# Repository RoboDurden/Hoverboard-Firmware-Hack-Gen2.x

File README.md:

# find your board with the 'interactive search' on the [Wiki](https://github.com/RoboDurden/Hoverboard-Firmware-Hack-Gen2.x/wiki) here :-)

# study the [Wiki](https://github.com/RoboDurden/Hoverboard-Firmware-Hack-Gen2.x/wiki) before opening a new issue !
***

### code moved to [Hoverboard-Firmware-Hack-Gen2.x-GD32](https://github.com/RoboDurden/Hoverboard-Firmware-Hack-Gen2.x-GD32) !!
### MM32 port go here [Hoverboard-Firmware-Hack-Gen2.x-MM32](https://gitlab.com/ailife8881/Hoverboard-Firmware-Hack-Gen2.x-MM32)) (FOC, speed/torque/position-control, ODrive CANSimple over UART, uartBus protocol, pinFinder over uart/browser UI)
#### MM32 EFeru FOC port go here [MM32SPIN05_Hoberboard_hack](https://github.com/trondin/MM32SPIN05_Hoberboard_hack) (no foc,but EFeru uart protocol)
both MM32 firmwares run on this $4.4 (+$5 shipping) pair of Gen2.4.2 boards: https://www.aliexpress.com/item/1005005959910034.html (tell me if you find a likewise offer that ships to Germany/EU)
***

### 2024/02/18: board numbering changed from Gen2.x to Gen2.t.v
Gen2.1.4xf = split board . target 1 . version 4 x=64kb, f=FOC capable.

The s(32kB)/x(64kB) flag and the f flag are for information only.

Targets are the Keil targets:
- 1 gd32f130 
- 2 gd/stm32f103 
- 3 gd32e230 
- 4 mm32spin0x 
- 5 lks32

## 2024/1/10 the following layouts are ready to use (99%):

- Gen2.1.1 (ex2.0)
- Gen2.1.3 (ex2.2) https://github.com/RoboDurden/Hoverboard-Firmware-Hack-Gen2.x/issues/5
- Gen2.1.4 (ex2.3) https://github.com/RoboDurden/Hoverboard-Firmware-Hack-Gen2.x/issues/20
- Gen2.1.7.1 (ex2.6.1) https://github.com/RoboDurden/Hoverboard-Firmware-Hack-Gen2.x/issues/49
- Gen2.1.8 (ex2.10) https://github.com/RoboDurden/Hoverboard-Firmware-Hack-Gen2.x/issues/25
- Gen2.1.11 (ex2.13) https://github.com/RoboDurden/Hoverboard-Firmware-Hack-Gen2.x/issues/33
- Gen2.1.16 (ex2.18) https://github.com/RoboDurden/Hoverboard-Firmware-Hack-Gen2.x/issues/40

layouts worth testing (with a 2A cc constant current power supply / dcdc-step-down converter | 1.5 42V charger):

- Gen2.1.2 (ex2.1) this repo here was a fork from a running 2.1 firmware
- Gen2.1.5 (ex2.4) https://github.com/RoboDurden/Hoverboard-Firmware-Hack-Gen2.x/issues/3
- Gen2.3.1 (ex2.7) https://github.com/RoboDurden/Hoverboard-Firmware-Hack-Gen2.x/issues/16
- Gen2.1.9 (ex2.11) https://github.com/RoboDurden/Hoverboard-Firmware-Hack-Gen2.x/issues/27
- Gen2.1.13 (ex2.15) https://github.com/RoboDurden/Hoverboard-Firmware-Hack-Gen2.x/issues/38
- Gen2.1.18 (ex2.20) https://github.com/RoboDurden/Hoverboard-Firmware-Hack-Gen2.x/issues/58
  
### Update 2.x:
- This is a fork from https://github.com/krisstakos/Hoverboard-Firmware-Hack-Gen2.1
- with different defines_2-x.h for two different board layouts :-) 
- Simply set `#define LAYOUT x` to your 2.x board in `Inc/config.h` :-))
- You can download compiled binaries [here](BinariesReadyToFlash/) (the Dummy-firmwares will ignore uart speed and will repeat speed from -300 to 300 instead)
- Binaries probably not yet working: [BinariesToTest/](BinariesToTest/)
- Make sure your board is one of the supported layouts ! **Wrong pin assignments can shortcut the battery and kill the mosfets !!**

#### Update 2.1:
- That's a fork from https://github.com/flo199213/Hoverboard-Firmware-Hack-Gen2
- Compiles with Keil version 6 :-))

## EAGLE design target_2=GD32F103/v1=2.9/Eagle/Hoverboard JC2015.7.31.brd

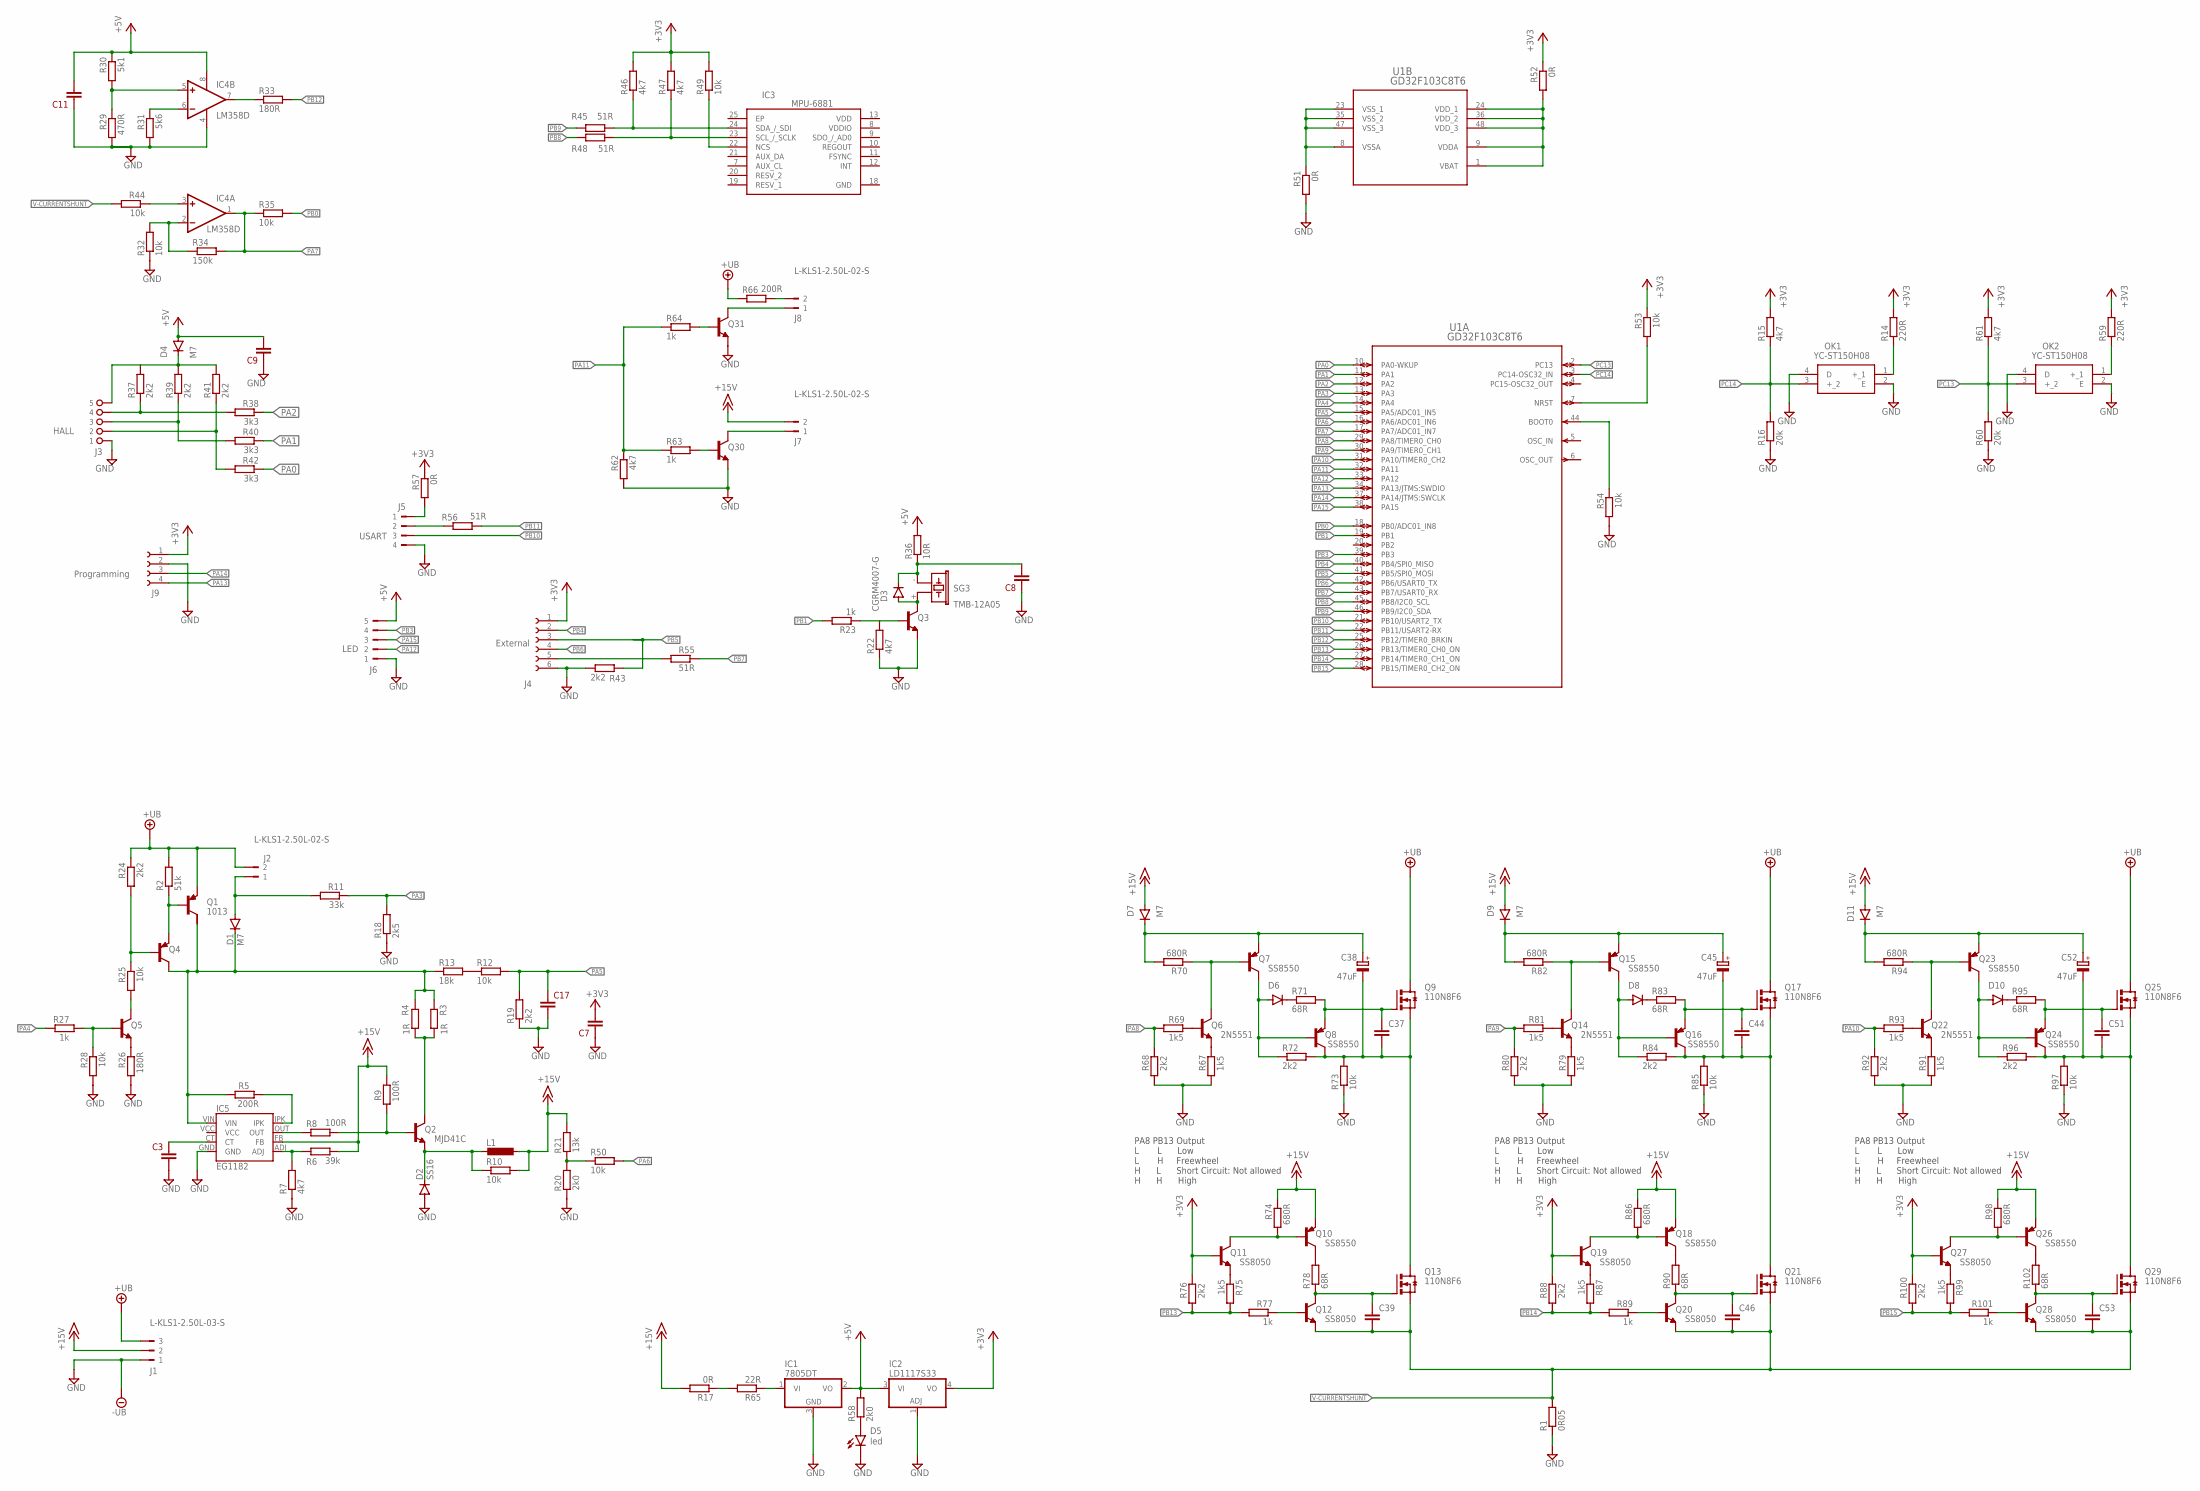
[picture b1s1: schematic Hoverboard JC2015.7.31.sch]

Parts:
C3, C7, C8, C9, C11, C17, C37, C39, C44, C46, C51, C53: C-EUC0603; C0603
C38, C45, C52: 47uF; E1,8-4
D1, D4, D7, D9, D11: M7; SOD-123_MINI-SMA
D2: SS16; DO-214AC
D3: CGRM4007-G; SOD-123_MINI-SMA
D5: led; PLCC2
D6, D8, D10: DIODE-MINIMELF; MINIMELF
IC1: 7805DT; TO252
IC2: LD1117S33; SOT223
IC3: MPU-6881; QFN40P300X300X95-25N
IC4: LM358D; SO08
IC5: EG1182
J1: L-KLS1-2.50L-03-S
J2, J7, J8: L-KLS1-2.50L-02-S
J3: HALL; ST05-1
J4: External; FE06-1
J5: USART; L-KLS1-2.50L-04-S
J6: LED; L-KLS1-2.50L-05-S
J9: Programming; FE04-1
L1: L-EU6000-XXX-RC; 6000-XXXX-RC
OK1, OK2: YC-ST150H08
Q1: 1013; SOT89
Q2: MJD41C; DPAK
Q3, Q5, Q30, Q31: MMBT5551LT1-NPN-SOT23-BEC; SOT23-BEC
Q4: MMBT540LT1-PNP-SOT23-BEC; SOT23-BEC
Q6, Q14, Q22: 2N5551; SOT23-BEC
Q7, Q8, Q10, Q15, Q16, Q18, Q23, Q24, Q26: SS8550; SOT23
Q9, Q13, Q17, Q21, Q25, Q29: 110N8F6; TO220BV
Q11, Q12, Q19, Q20, Q27, Q28: SS8050; SOT23-BEC
R1: 0R05; R2512
R2: 51k; R0805
R3, R4: 1R; R1206
R5: 200R; R0805
R6: 39k; R0805
R7, R15, R22, R46, R47, R61, R62: 4k7; R0805
R8, R9: 100R; R0805
R10, R12, R25, R28, R32, R35, R44, R49, R50, R53, R54, R73, R85, R97: 10k; R0805
R11: 33k; R0603
R13: 18k; R0805
R14, R59: 220R; R0805
R16, R60: 20k; R0805
R17: 0R; R1206
R18: 2k5; R0805
R19, R24, R37, R39, R41, R43, R68, R72, R76, R80, R84, R88, R92, R96, R100: 2k2; R0805
R20, R58: 2k0; R0805
R21: 13k; R0805
R23, R27, R63, R64, R77, R89, R101: 1k; R0805
R26, R33: 180R; R0805
R29: 470R; R0805
R30: 5k1; R0805
R31: 5k6; R0805
R34: 150k; R0805
R36: 10R; R0805
R38, R40, R42: 3k3; R0805
R45, R48, R55, R56: 51R; R0805
R51, R52, R57: 0R; R0805
R65: 22R; R2512
R66: 200R; R2512
R67, R69, R75, R79, R81, R87, R91, R93, R99: 1k5; R0805
R70, R74, R82, R86, R94, R98: 680R; R0805
R71, R78, R83, R90, R95, R102: 68R; R0805
SG3: TMB-12A05; TMB12A
U1: GD32F103C8T6; LQFP48-7X7MM; MANUFACTURER_PART_NUMBER GD32F103C8T6

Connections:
+3V3: C7.2, IC2.4 (VO), J4.1, J9.1, Q11.B, Q19.B, Q27.B, R14.2, R15.2, R46.2, R47.2, R49.2, R52.1, R53.1, R57.1, R59.2, R61.2, R76.2, R88.2, R100.2
+5V: C9.2, C11.2, D4.A, IC1.2 (VO), IC2.3 (VI), IC4.8 (V+), J6.5, R30.1, R36.2, R58.2
+15V: D7.A, D9.A, D11.A, IC5.FB, J1.2, J7.2, L1.1, Q10.2 (E), Q18.2 (E), Q26.2 (E), R6.2, R9.1, R10.2, R17.2, R21.1, R74.1, R86.1, R98.1
+UB: J1.3, J2.2, Q1.3 (E), Q9.D, Q17.D, Q25.D, R2.2, R24.1, R66.1
GND: C3.2, C7.1, C8.1, C9.1, C11.1, C17.2, D2.A, D5.C, IC1.3 (GND), IC2.1 (ADJ), IC4.4 (V-), IC5.GND, J1.1, J3.1, J4.6, J5.4, J6.1, J9.2, OK1.2 (E), OK1.4 (D), OK2.2 (E), OK2.4 (D), Q3.E, Q30.E, Q31.E, R1.1, R7.1, R16.1, R18.1, R19.1, R20.2, R22.1, R26.2, R28.2, R29.2, R31.2, R32.1, R43.1, R51.2, R54.2, R60.1, R62.2, R67.1, R68.1, R73.1, R79.1, R80.1, R85.1, R91.1, R92.1, R97.1
unnamed: D1.A, J2.1, R11.2
unnamed: IC3.24 (SDA_/_SDI), R45.1, R46.1
unnamed: D1.C, IC5.VIN, Q4.C, R3.1, R4.1, R5.2, R13.1
unnamed: R12.1, R13.2
unnamed: Q1.1 (B), Q4.E, R2.1
unnamed: Q4.B, R24.2, R25.1
unnamed: Q14.E, R79.2
unnamed: IC5.ADJ, R6.1, R7.2
unnamed: Q2.1 (B), R8.2, R9.2
unnamed: IC5.OUT, R8.1
unnamed: C3.1, IC5.CT
unnamed: Q2.4 (C), R3.2, R4.2
unnamed: D2.C, L1.2, Q2.3 (E), R10.1
unnamed: IC1.1 (VI), R65.1
unnamed: IC5.IPK, R5.1
unnamed: OK1.1 (+_1), R14.1
unnamed: R17.1, R65.2
unnamed: Q14.B, R81.2
unnamed: R20.1, R21.2, R50.1
unnamed: IC3.23 (SCL_/_SCLK), R47.1, R48.1
unnamed: Q3.B, R22.2, R23.1
unnamed: Q5.C, R25.2
unnamed: D3.A, Q3.C, SG3.+ (1)
unnamed: C8.2, D3.C, R36.1, SG3.- (2)
unnamed: Q5.E, R26.1
unnamed: Q5.B, R27.1, R28.1
unnamed: IC3.22 (NCS), R49.1
unnamed: IC4.5 (+IN), R29.1, R30.2
unnamed: IC4.6 (-IN), R31.1
unnamed: IC4.2 (-IN), R32.2, R34.1
unnamed: R51.1, U1.8 (VSSA), U1.23 (VSS_1), U1.35 (VSS_2), U1.47 (VSS_3)
unnamed: IC4.3 (+IN), R44.1
unnamed: IC4.7 (OUT), R33.1
unnamed: R52.2, U1.1 (VBAT), U1.9 (VDDA), U1.24 (VDD_1), U1.36 (VDD_2), U1.48 (VDD_3)
unnamed: R53.2, U1.7 (NRST)
unnamed: J3.4, R37.1, R38.2
unnamed: D4.C, J3.5, R37.2, R39.2, R41.2
unnamed: R54.1, U1.44 (BOOT0)
unnamed: J3.3, R39.1, R40.2
unnamed: J8.2, R66.2
unnamed: J3.2, R41.1, R42.2
unnamed: J4.5, R55.2
unnamed: J5.1, R57.2
unnamed: D5.A, R58.1
unnamed: OK2.1 (+_1), R59.1
unnamed: J7.1, Q30.C
unnamed: Q30.B, R63.2
unnamed: J8.1, Q31.C
unnamed: Q31.B, R64.1
unnamed: Q6.E, R67.2
unnamed: Q6.B, R69.2
unnamed: Q6.C, Q7.1 (B), R70.1
unnamed: C38.+, D7.C, Q7.2 (E), R70.2
unnamed: D6.A, Q7.3 (C), Q8.1 (B), R72.1
unnamed: D6.C, R71.1
unnamed: C37.2, Q8.2 (E), Q9.G, R71.2
unnamed: C37.1, C38.-, Q8.3 (C), Q9.S, Q13.D, R72.2, R73.2
unnamed: Q10.1 (B), Q11.C, R74.2
unnamed: Q14.C, Q15.1 (B), R82.1
unnamed: Q10.3 (C), R78.2
unnamed: C39.2, Q12.C, Q13.G, R78.1
unnamed: C45.+, D9.C, Q15.2 (E), R82.2
unnamed: D8.A, Q15.3 (C), Q16.1 (B), R84.1
unnamed: Q11.E, R75.1
unnamed: Q12.B, R77.1
unnamed: D8.C, R83.1
unnamed: C44.2, Q16.2 (E), Q17.G, R83.2
unnamed: C44.1, C45.-, Q16.3 (C), Q17.S, Q21.D, R84.2, R85.2
unnamed: Q18.1 (B), Q19.C, R86.2
unnamed: Q18.3 (C), R90.2
unnamed: C46.2, Q20.C, Q21.G, R90.1
unnamed: Q19.E, R87.1
unnamed: Q20.B, R89.1
unnamed: Q22.E, R91.2
unnamed: Q22.B, R93.2
unnamed: Q22.C, Q23.1 (B), R94.1
unnamed: C52.+, D11.C, Q23.2 (E), R94.2
unnamed: D10.A, Q23.3 (C), Q24.1 (B), R96.1
unnamed: D10.C, R95.1
unnamed: C51.2, Q24.2 (E), Q25.G, R95.2
unnamed: C51.1, C52.-, Q24.3 (C), Q25.S, Q29.D, R96.2, R97.2
unnamed: Q26.1 (B), Q27.C, R98.2
unnamed: Q26.3 (C), R102.2
unnamed: C53.2, Q28.C, Q29.G, R102.1
unnamed: Q27.E, R99.1
unnamed: Q28.B, R101.1
unnamed: J5.2, R56.2
PA0: R42.1, U1.10 (PA0-WKUP)
PA1: R40.1, U1.11 (PA1)
PA2: R38.1, U1.12 (PA2)
PA3: R11.1, R18.2, U1.13 (PA3)
PA4: R27.2, U1.14 (PA4)
PA5: C17.1, R12.2, R19.2, U1.15 (PA5/ADC01_IN5)
PA6: R50.2, U1.16 (PA6/ADC01_IN6)
PA7: IC4.1 (OUT), R34.2, R35.1, U1.17 (PA7/ADC01_IN7)
PA8: R68.2, R69.1, U1.29 (PA8/TIMER0_CH0)
PA9: R80.2, R81.1, U1.30 (PA9/TIMER0_CH1)
PA10: R92.2, R93.1, U1.31 (PA10/TIMER0_CH2)
PA11: R62.1, R63.1, R64.2, U1.32 (PA11)
PA12: J6.2, U1.33 (PA12)
PA13: J9.4, U1.34 (PA13/JTMS:SWDIO)
PA14: J9.3, U1.37 (PA14/JTMS:SWCLK)
PA15: J6.3, U1.38 (PA15)
PB0: R35.2, U1.18 (PB0/ADC01_IN8)
PB1: R23.2, U1.19 (PB1)
PB3: J6.4, U1.39 (PB3)
PB4: J4.2, U1.40 (PB4/SPI0_MISO)
PB5: J4.3, R43.2, U1.41 (PB5/SPI0_MOSI)
PB6: J4.4, U1.42 (PB6/USART0_TX)
PB7: R55.1, U1.43 (PB7/USART0_RX)
PB8: R48.2, U1.45 (PB8/I2C0_SCL)
PB9: R45.2, U1.46 (PB9/I2C0_SDA)
PB10: J5.3, U1.21 (PB10/USART2_TX)
PB11: R56.1, U1.22 (PB11/USART2-RX)
PB12: R33.2, U1.25 (PB12/TIMER0_BRKIN)
PB13: R75.2, R76.1, R77.2, U1.26 (PB13/TIMER0_CH0_ON)
PB14: R87.2, R88.1, R89.2, U1.27 (PB14/TIMER0_CH1_ON)
PB15: R99.2, R100.1, R101.2, U1.28 (PB15/TIMER0_CH2_ON)
PC13: OK2.3 (+_2), R60.2, R61.1, U1.2 (PC13)
PC14: OK1.3 (+_2), R15.1, R16.2, U1.3 (PC14-OSC32_IN)
V-CURRENTSHUNT: C39.1, C46.1, C53.1, Q12.E, Q13.S, Q20.E, Q21.S, Q28.E, Q29.S, R1.2, R44.2

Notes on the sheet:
PA8 PB13 Output L L Low L H Freewheel H L Short Circuit: Not allowed H H High

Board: 2 copper layers, 178 parts (8 on the bottom side), 126 nets, no tracks yet.

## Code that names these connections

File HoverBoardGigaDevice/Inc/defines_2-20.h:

#ifndef DEFINES_2_x_H
#define DEFINES_2_x_H

#ifdef MASTER_OR_SINGLE		// layout 2.2 and 2.7 have buzzer on the slave board.
	#define HAS_BUZZER
#endif
#define TODO_PIN PF4


// by AILIFE4798

#define HALL_A		PA0
#define HALL_B		PA1
#define HALL_C		PB11
#define PHASE_A		PB1
#define PHASE_B		PB0
#define PHASE_C		PA7

#define LED_RED		PA15
#define LED_ORANGE		PB3
#define LED_GREEN		PB4
#define UPPER_LED		PB5
#define LOWER_LED		PB8
#define BUZZER		PB9
#define VBATT		PA4
#define CURRENT_DC		PA6
#define SELF_HOLD		PB2
#define BUTTON		PA5


#define HAS_USART0	// tx=PB6,rx=PB7	uncomment to connect via 19200 baud serial
#define HAS_USART1	// tx=PA2,rx=PA3	uncomment to connect via 19200 baud serial





// Brushless Control DC (BLDC) defines
#define BLDC_GH PA8		// green	, Tommyboi2001 all bldc pins same as 2.0
#define BLDC_GL PB13		
#define BLDC_BH PA9			// blue
#define BLDC_BL PB14		
#define BLDC_YH PA10			// yellow
#define BLDC_YL PB15		
#define TIMER_BLDC_PULLUP	GPIO_PUPD_NONE	// robo: not sure if some boards indeed nned GPIO_PUPD_PULLUP like 2.2 or 2.3


// Timer BLDC short circuit emergency shutoff define
//#define TIMER_BLDC_EMERGENCY_SHUTDOWN	P_UNKOWN


// GD32F130 USART0 TX/RX:	(PA9/PA10)AF1	, (PB6/PB7)AF0 , 	(PA2/PA3)AF1 , (PA14/PA15)AF1 GD32F130x4 only!
#ifdef HAS_USART0
	#define USART0_TX	PA11
	#define USART0_RX	PA12
	
	//#define USART0_MASTERSLAVE		// uncomment if this usart is used for master-slave communication
	#define USART0_REMOTE						// uncomment if this usart is used for optional remote control
#endif


// GD32F130 USART1 GD32F130 TX/RX: (PA14/PA15)AF1 , (PA2,PA3)AF1	, (PA8/PB0)AlternateFunction4
#ifdef HAS_USART1
	#define USART1_TX		PA3
	#define USART1_RX		PA2
	
	#define USART1_MASTERSLAVE		// uncomment if this usart is used for master-slave communication
	//#define USART1_REMOTE				// uncomment if this usart is used for optional remote control
#endif


#endif

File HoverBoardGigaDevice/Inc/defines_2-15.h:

#ifdef MASTER_OR_SINGLE		// layout 2.2 and 2.7 have buzzer on the slave board.
	#define HAS_BUZZER
#endif

/* GD32F130 48pin possible IO pins: 
	C13 C14 C15 F0 F1 A0 A1 A2 
	A3 A4 A5 A6 A7 B0 B1 B2 B10 B11
	B12 B13 B14 B15 A8 A9 A10 A11 A12 A13 F6 F7
	A14 A15 B3 B4 B5 B6 B7 B8 B9 
	
	mostly used for 6 BLDC mosfet pins: B13 B14 B15 A8 A9 A10
	mostly used for USART0: B6 B7
	mostly used for USART1: A2 A3
	ST-Flash pins: A13 A14 (also used as green and red led on 2.2)
	
	so mostly available for other use:	
	C13 C14 C15 F0 F1 A0 A1 A4 A5 A6 A7 B0 B1 B2 B10 B11 B12 A11 F6 F7 A12 A15 B3 B4 B5 B8 B9 
	so available for analog input:
	A0 A1 A2 A3 A4 A5 A6 A7 B0 B1 	
*/

#define TODO_PIN PF4	// PF4 is only accessible on the largest GD32F130Rx LQFP64 pinouts mcu

// LED defines
#define LED_GREEN PA15	// robo, from andyshmandy pin tracing image
#define LED_ORANGE PB3	// colors might be wrong !
#define LED_RED PB4

#define UPPER_LED	PB5		// robo, from andyshmandy pin tracing image
#define LOWER_LED	PF1		// upper and lower might be swaped


// Mosfet output, little onboard led
#define MOSFET_OUT	TODO_PIN	// robo might be the blue led inside the hover motors

// Brushless Control DC (BLDC) defines
#define BLDC_GH PA10		// green	, Tommyboi2001 all bldc pins same as 2.0
#define BLDC_GL PB15		
#define BLDC_BH PA9		// blue
#define BLDC_BL PB14		
#define BLDC_YH PA8		// yellow
#define BLDC_YL PB13		
#define TIMER_BLDC_PULLUP	GPIO_PUPD_NONE	// robo: not sure if some boards indeed nned GPIO_PUPD_PULLUP like 2.2 or 2.3


// Timer BLDC short circuit emergency shutoff define
#define TIMER_BLDC_EMERGENCY_SHUTDOWN	PB12		// robo from pin tracing photo

// Hall sensor defines
#define HALL_A	PC14
#define HALL_B	PA1
#define HALL_C	PB11

// GD32F130 USART0 TX/RX:	(PA9/PA10)AF1	, (PB6/PB7)AF0 , 	(PA2/PA3)AF1 , (PA14/PA15)AF1 GD32F130x4 only!
#define HAS_USART0	// uncomment if this layout has a usart0
#ifdef HAS_USART0
	#define USART0_TX	PB6		// robo, from andyshmandy pin tracing image
	#define USART0_RX	PB7
	
	//#define USART0_MASTERSLAVE		// uncomment if this usart is used for master-slave communication
	#define USART0_REMOTE						// uncomment if this usart is used for optional remote control
#endif


// GD32F130 USART1 GD32F130 TX/RX: (PA14/PA15)AF1 , (PA2,PA3)AF1	, (PA8/PB0)AlternateFunction4
#define HAS_USART1	// uncomment if this layout has a usart1
#ifdef HAS_USART1
	#define USART1_TX		PA2		// robo, from andyshmandy pin tracing image
	#define USART1_RX		PA3
	
	#define USART1_MASTERSLAVE		// uncomment if this usart is used for master-slave communication
	//#define USART1_REMOTE				// uncomment if this usart is used for optional remote control
#endif



// ADC defines
#define VBATT	PA4			// robo just guessing, maybe PA0 PA4 PA5 
	
#define CURRENT_DC	PA6		// robo from pin tracing photo

#define PHASE_CURRENT_G	PB1		// robo from pin tracing photo, maybe wong order
#define PHASE_CURRENT_B	PB0		
#define PHASE_CURRENT_Y	PA7		



// Self hold defines
#define SELF_HOLD	PB2 	// robo from pin tracing photo

// Button defines
#define BUTTON	PA5		// robo from pin tracing photo

#ifdef HAS_BUZZER
	// Buzzer defins
	#define BUZZER	PF0		// robo from pin tracing photo
#endif

#ifdef MASTER
	// Charge state defines
	#define CHARGE_STATE	TODO_PIN
#endif

// Debug pin defines -  no longer has any function in code !
#define DEBUG_PIN TODO_PIN

// photo diodes / light barriers on the backside
#define PHOTO_L_PIN		PA11
#define PHOTO_R_PIN		PB10

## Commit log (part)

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2023-09-26 2.11 added
2023-09-26 defines_2-11.h added
2023-09-26 speed = 0 for TEST_HALL2LED
2023-09-26 IRS2003 for 2.11
2023-09-26 NREST for SWD rework
2023-09-28 2.12 added
2023-09-28 2.12
2023-10-01 flashing without the RST pin
2023-10-01 pin tracing
2023-10-01 thanks to DerPinguin77
2023-10-03 video demonstration
2023-10-14 watch 2023/10/14 youtube video
2023-10-14 new test binaries
2023-10-19 new arduino PPM example provided from user Pacraf
2023-10-20 new binaries
2023-10-22 now wState in serial protocol to turn onOff leds and Shutoff
2023-10-22 outdated.
2023-10-22 uartbus
2023-10-23 2.2 now 99% working :-)
2023-10-24 code cleanup master-slave seems to work smoothly again.
2023-10-25 wrong esp32 tx pin
2023-10-28 more pin tracing
2023-10-28 image updates
2023-10-29 2.10 added
2023-10-29 buzzer pin added
2023-10-29 buzzer now also for SINGLE
2023-10-30 hoverboard 2.10 single UartBus id0 uart1.bin
2023-10-30 new HOLD pin PB2
2023-10-30 hall A and C swapped
2023-10-30 old hall order
2023-10-31 new pin defines PA12, PA15, PB3
2023-10-31 both hall orders
2023-10-31 testing
2023-10-31 hall order now correct
2023-10-31 new arduino style PA15, etc.
2023-10-31 new arduino style digitalWrite/Read ..
2023-10-31 img updates
2023-11-01 defines_2-0.h update to new Arduino format
2023-11-01 2.10 led now working ?
2023-11-01 different led defines for master and slave
2023-11-01 new Arduino example Test_4Wheeler.ino
2023-11-02 testing uartBus with 4Wheeler.ino
2023-11-02 bug in Receive() fixed
2023-11-02 hoverserial.h Receive() bug fixed.
2023-11-02 hoverserial.h Receive bug fixed
2023-11-02 2.0 single uartBus id0 DEBUG_LED 6s
2023-11-02 new layout 2.13
2023-11-02 pin updates
2023-11-02 mcu manuals updated
2023-11-02 2.10 ready
2023-11-03 REMOTE_UARTBUS needs Schottky diodes
2023-11-03 slave powerOff now works on button OnOff
2023-11-03 now REMOTE_UART working smoothly again :-)
2023-11-03 now control multiple MASTER via REMOTE_UARTBUS :-)
2023-11-29 2.14 added
2023-11-29 gen2.14
2023-11-29 2.14
2023-11-29 2.14 first test binary
2023-12-02 2.15 added
2023-12-02 //VBATT now compiles
2023-12-12 Update defines_2-15.h
    Tested this defines using REMOTE_DUMMY uncommented and it is working great
2023-12-13 2.15 pin tracing
2023-12-14 2.16 added
2023-12-19 2.17 added
2023-12-19 Layout 2-17 - RemoteDummy working #44
2023-12-19 #44 - More changes to include defines file in the project
2023-12-21 scaled down to save space
2023-12-23 Update defines_2-17.h #44
    -Confirmed a few more ADC defines.
    -Updates some comments for this specific layout
    -Added photo of the slave board and confirmed that there are no LEDs
2023-12-24 altnerate function for usart0 fixed
2023-12-24 alternate function fixed for usart0
2023-12-24 old hoverserial.h broke RemoteUartBus :-(
2023-12-24 latest library
2023-12-26 Document HoverSetupEsp32 method for better clarity
    -Changed method variable names to hopefully avoid confusing GPIO Port number with ESP32 pin numbers.
    -Added comments to help clarify confusion.
2023-12-26 Remove references to 'port' for GPIO in Arduino examples
    Updates based on code review comments.
2023-12-28 2.18 added
2023-12-28 2.18
2023-12-31 better UartBus loop
2023-12-31 remove
2024-01-04 layout 2.6.1 added
2024-01-05 defines_2-6.h added
2024-01-05 test binaries for 2.6.1
2024-01-05 temp image delete
2024-01-05 2.6 updates
2024-01-06 2.6.1 all 6 hall combinations
2024-01-06 uart0 header
2024-01-06 2.6 hall correct
2024-01-06 current pin binaries
2024-01-06 2.6 complete ?
2024-01-08 add mm32spin target and changed layout2.6 pin
2024-01-08 target.h change
2024-01-08 sync define2.6
2024-01-08 2.8 added..
2024-01-08 2.8 still 75 errors
2024-01-08 inc files wrong in plqace deleted
2024-01-08 2.8 still 48 errors.
2024-01-08 2.8 down to 40 errors.
2024-01-08 2.8. 37 errors
2024-01-08 2.8 down to 36 errors
2024-01-08 added hal lib to project file
2024-01-08 add hallib .h files
2024-01-08 Revert "2.8 down to 36 errors"
    This reverts commit 1094b7cd4ceb24d11eaf3d9595d0e1da31b49543.
2024-01-08 added include path for compiler target option
2024-01-08 Revert "Revert "2.8 down to 36 errors""
    This reverts commit a754bf75f15eea11448a4f6f0bc7c61efee4d01b.
2024-01-08 back to 36 error and hal lib included in target option
2024-01-08 changed define2.8.h and target.h to include some hal library
2024-01-09 edited target.h, down to 34 error
2024-01-09 2.8 down to 34 errors
2024-01-09 2.8 down to 22 errors
2024-01-10 code moved to partner repo
2024-01-10 binaries
2024-01-10 upload
2024-01-10 test
2024-01-13 first autodetect binaries !!!
2024-01-13 autodetect binaries !!!
2024-01-14 autodetect with hall + led + buzzer + adc + hold
2024-01-14 2.19 added
2024-01-14 2.19
2024-01-14 autodetect.bin complete !!!
2024-01-15 autodetect tested from 24V to 29V power supply 2A constant current
2024-01-19 images upated
2024-01-19 autodetect updated
2024-01-19 now with phase current autodetect
2024-01-19 uart0
2024-01-20 now VBatt first
2024-01-20 testing vbatt
2024-01-21 better autodetect
2024-01-22 better autodetect binaries
2024-02-04 2.20 added
2024-02-04 2.20 update
2024-02-06 32f103 binaries
2024-02-08 2.21 added
2024-02-16 beware of these hoverboards
2024-02-16 h6 eco pcb
2024-02-16 do not buy
2024-02-18 new board numbering
2024-02-22 Gen2.1.13 test binaries
2024-02-25 gen2_6.1
2024-04-08 pinFinder
2024-04-09 please send me your serial numbers
2024-04-18 delete
2024-04-18 2.1.12 added
2024-04-18 2.2.2
2024-04-22 flash header
2024-05-01 different stage order
2024-05-01 pinmode input_pullup and pulldown..
2024-05-02 2.1.6.1 test binaries added
2024-05-03 udpate !
2024-05-20 2.2.3 added
2024-05-21 from JohMah/Hoverboard-JC2015.7.31.V2.0-Hack/
2024-08-26 Gen2.1.20 added
2024-08-26 found in
2024-08-30 2.1.20
2024-09-03 gen2.1.21
2024-09-23 2.4.5 added
2024-09-25 uart pins
2024-09-25 2.4.5
2024-09-25 2.4.5 removed
2024-09-30 gen2.4.5
2024-09-30 2.5.4
2025-02-08 old uart protocol on a slave with no on/off button
2025-05-01 autodecting hall pins and hall order :-)
2025-05-01 autodetect now hall and led :-)
2025-05-01 #define LAYOUT_SUB 1 for gen 2.6.1 added
2025-05-01 autodetecting hall pins and order :-)
2025-05-01 autodetect now with hall and led :-)
2025-05-01 autodetect now hall + led
2025-05-01 autodetect now hall + led + buzzer
2025-05-01 init
2025-05-01 code moved
2025-05-01 defines updated
2025-05-01 warning autodetect set in config.h !
2025-05-01 autodetect prints hal pins to PB6 19200 baud
2025-05-01 autodetect now hall + led + vbatt + currentDc
2025-05-01 gd32f103 25 errors :-/
2025-05-01 autodetect now hall + led + buzzer :-)
2025-05-01 added define 2.20
2025-05-01 Add PlatformIO config file
    Make it possible to build project using VSCode / PlatformIO
2025-05-01 autodetect now with phase currents
2025-05-01 only 3x hall and 6x phase needed to compile
2025-05-01 2.1.6.1 added
2025-05-01 MM32 support
2025-05-01 gd32f103 20 errors left from JohMah port
2025-05-01 new board numbering Gen2.target.version
2025-05-01 bettter TEST_HALL2LED
2025-05-01 autodetect: pullup/down now also for led stage
2025-05-01 stm32f103 autodetect
2025-05-01 autodetect now VBatt first
2025-05-01 autodetect ready
2025-05-01 now with SELF_HOLD :-)
2025-05-01 autodetect: hall + led + buzzer + adc + hold
2025-05-01 autodetect complete !
2025-05-01 old RemoteUart working again ?
2025-05-01 better autodetect with autodetect.ino !
2025-05-01 autodetect :-)
2025-05-01 autodetect hall bug resolved
2025-05-01 youtube video
2025-05-01 autodetect complete :-)
2025-05-01 autodetect tested with 24V to 29V power supply
2025-05-01 platformIO now compiling for GD32F130
2025-05-01 memory optimization
2025-05-01 vbatt also on PA2 and PA3 :-(
2025-05-01 Add Layout Layout2-20 (Classy Walk)
    Tested with REMOTE_DUMMY and `#define BAT_CELLS 7`
    Only master board tested so far
2025-05-01 autodetect update
2025-05-01 vbatt added
2025-05-01 TARGET now defined in Keil "Options for target"
2025-05-01 hold detect rewritten
2025-05-01 autodetect menu and selfHold manual find option
2025-05-01 detecting back-current spike
2025-05-01 now with phase current autodetection
2025-05-01 platformio support
2025-05-01 GD32F103 target with 44 errors..
2025-05-01 button pullup
2025-05-01 udpate
2025-05-01 Remove comment about repo move
2025-05-28 2.1.22 added
2025-05-29 2.2.5 added
2025-05-30 photos from Kambodia91 stm32f103 swap added
2025-06-27 thanks
2025-06-27 no autodetect.ino needed, every serial terminal will do
2025-06-27 never tested on real hardware :-(
2025-06-27 never tested on real hardware!
2025-06-29 imu findings
2025-07-11 new boards
2025-07-11 new board
2025-07-11 translation by Gemini
2025-07-11 chinese translation
2025-07-22 2.3.3 added
2025-08-01 2.3.3
2025-08-06 images
2025-09-25 2.1.23 added
2025-09-25 2.1.24 added
2025-09-25 autodetect gd32f130 below 32kB again
2026-01-09 2.5.3 added
2026-04-28 2.2.20 binaries
2026-04-28 2.2.20

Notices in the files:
parts and their libraries:
COPYRIGHT: Copyright (C) 2018 Accelerated Designs. All rights reserved
